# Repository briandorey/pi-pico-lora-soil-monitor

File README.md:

# Allotment LoRa Wireless Moisture Monitor

This repository contains the hardware and software files for the allotment LoRa wireless moisture monitoring system that can be found on https://www.briandorey.com/post/pi-pico-lora-remote-soil-monitor

The system consists of a sender and receiver, both using a Raspberry Pi Pico and a LoRa wireless module. The sensor reads moisuture, temperature and humitidy values from a series of sensors and sends the data wirelessly to the receiver module using the LoRa wireless protocol.

## Components
###  1. AllotmentSender
   - Hardware: Includes the design and implementation of the sender's physical components.
   - Firmware: Software running on the sender hardware to read sensor data, update an e-paper display and send the data to the home receiver via a LoRa module.

### 2. Home Receiver
   - Hardware: Details about the receiver's physical components.
   - Firmware: Software running on the receiver hardware to handle incoming LoRa data and relay it to an MQTT broker

## License

MIT License

Copyright (c) 2025 Brian Dorey

Permission is hereby granted, free of charge, to any person obtaining a copy of this software and associated documentation files (the "Software"), to deal in the Software without restriction, including without limitation the rights to use, copy, modify, merge, publish, distribute, sublicense, and/or sell copies of the Software, and to permit persons to whom the Software is furnished to do so, subject to the following conditions:

The above copyright notice and this permission notice shall be included in all copies or substantial portions of the Software.

THE SOFTWARE IS PROVIDED "AS IS", WITHOUT WARRANTY OF ANY KIND, EXPRESS OR IMPLIED, INCLUDING BUT NOT LIMITED TO THE WARRANTIES OF MERCHANTABILITY, FITNESS FOR A PARTICULAR PURPOSE AND NONINFRINGEMENT. IN NO EVENT SHALL THE AUTHORS OR COPYRIGHT HOLDERS BE LIABLE FOR ANY CLAIM, DAMAGES OR OTHER LIABILITY, WHETHER IN AN ACTION OF CONTRACT, TORT OR OTHERWISE, ARISING FROM, OUT OF OR IN CONNECTION WITH THE SOFTWARE OR THE USE OR OTHER DEALINGS IN THE SOFTWARE.

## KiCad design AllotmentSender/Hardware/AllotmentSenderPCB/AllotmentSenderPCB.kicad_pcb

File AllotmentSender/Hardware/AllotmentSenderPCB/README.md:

# Allotment Sender

This directory contains the PCB files for the sender hardware. Full details for the allotment LoRa wireless moisture monitoring system that can be found on https://www.briandorey.com/post/pi-pico-lora-remote-soil-monitor

Subdirectories

- **bom**: HTML bom showing the locations of the components on the PCB.
- **production**: Gerber files and production files needed to manufacture the board.

The PCB was designed with Kicad version 9.0.1.

## KiCad

KiCad is an open-source software suite for creating electronic circuit designs and PCB layouts. It provides tools for schematic capture, PCB layout, and 3D visualization of the design.

You can download KiCad from the official website: https://kicad.org/download/

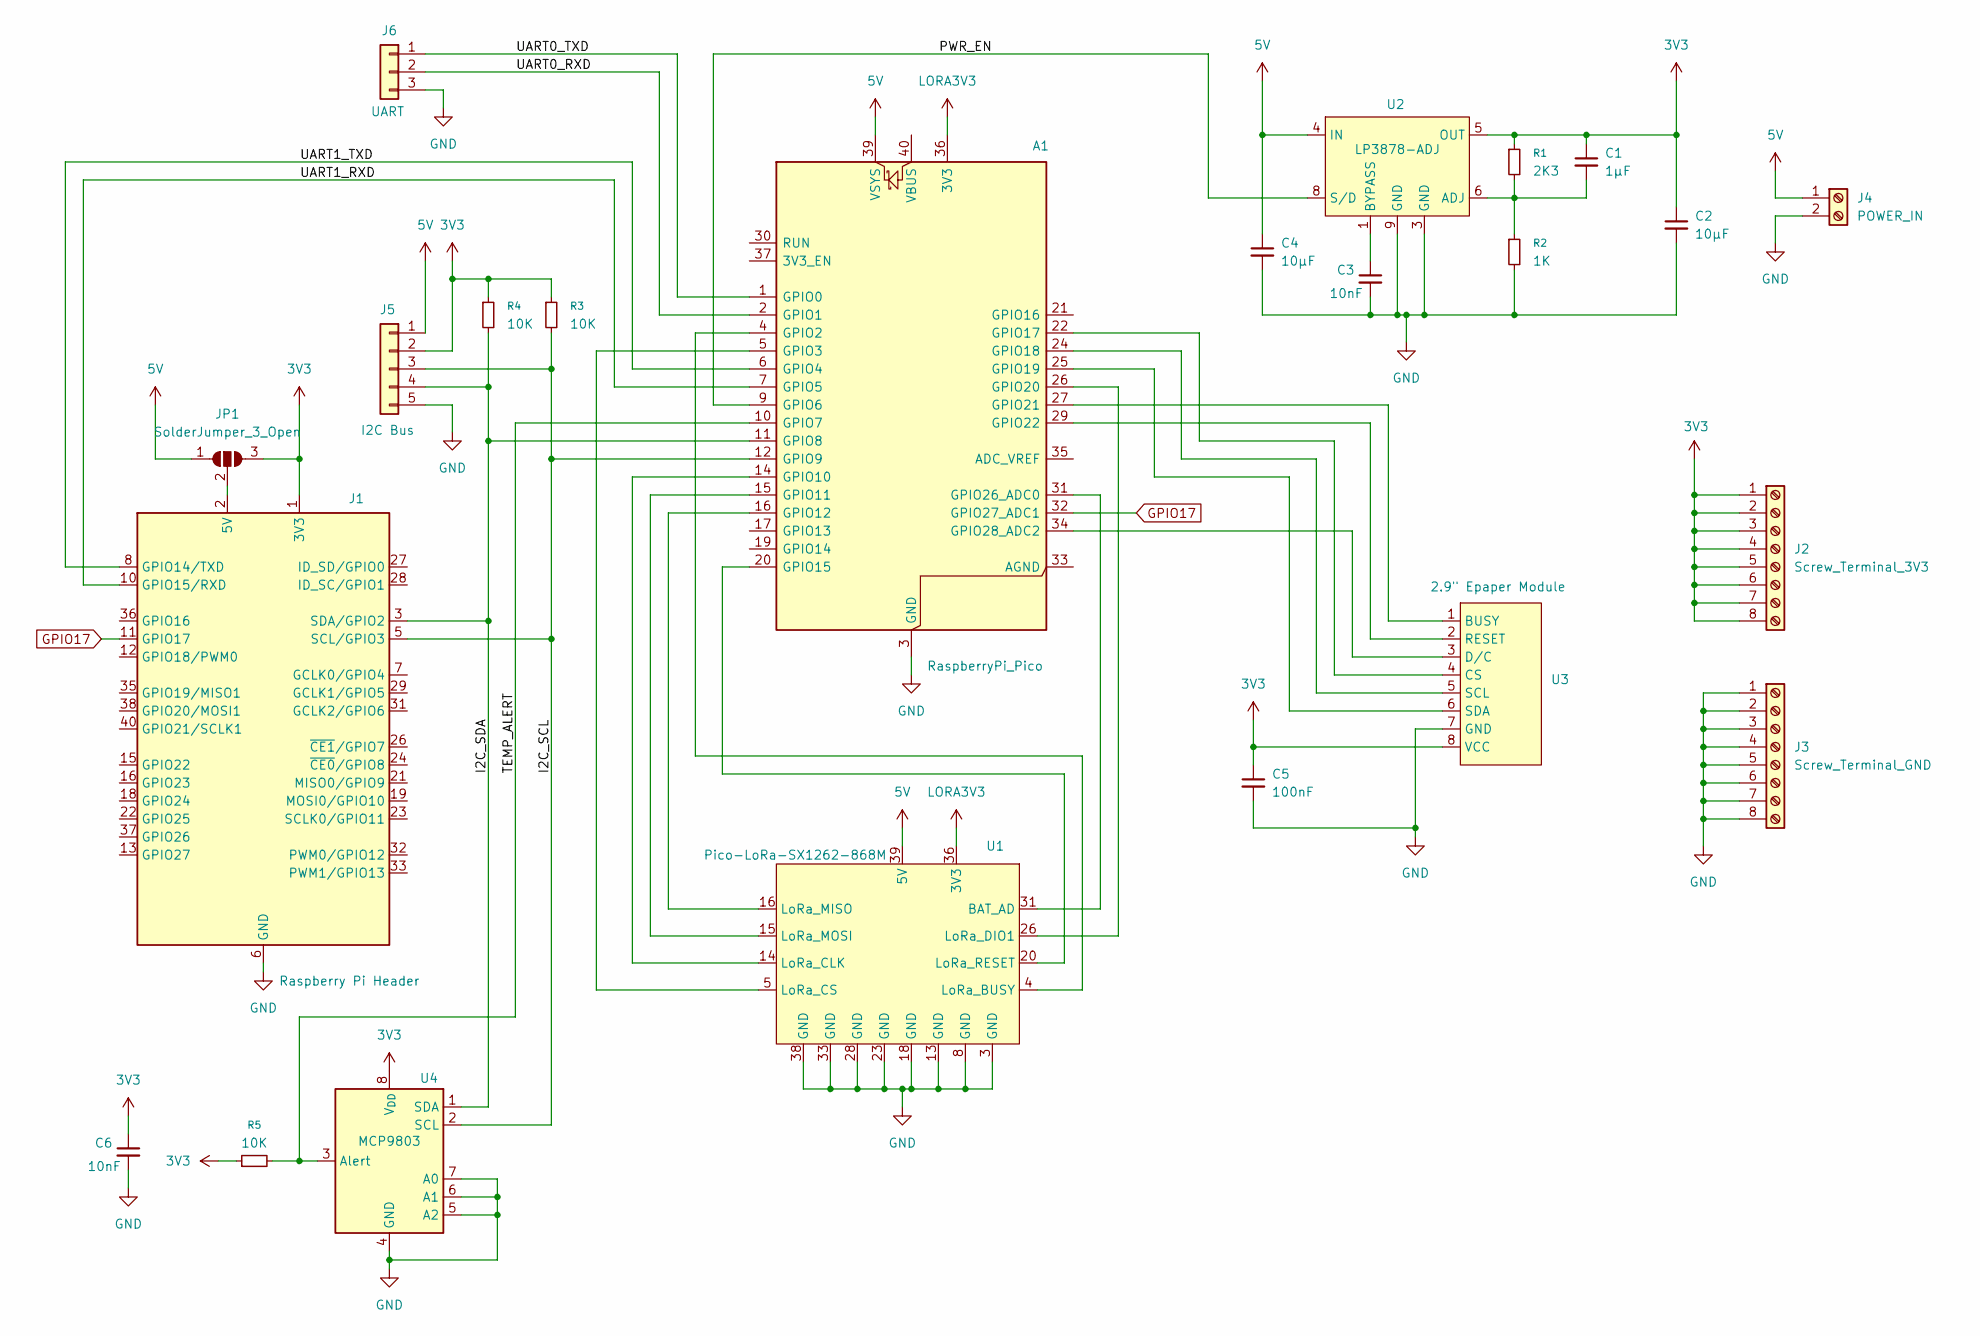
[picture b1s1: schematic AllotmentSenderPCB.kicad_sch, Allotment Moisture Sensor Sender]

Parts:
A1: RaspberryPi_Pico; RaspberryPi_Pico_Common_THT
C1: 1µF; C_0805_2012Metric
C2, C4: 10µF; C_0805_2012Metric
C3, C6: 10nF; C_0805_2012Metric
C5: 100nF; C_0805_2012Metric
J1: Raspberry Pi Header; Raspberry_Pi_Zero_Socketed_THT
J2: Screw_Terminal_3V3; PinHeader_1x08_P2.54mm_Vertical
J3: Screw_Terminal_GND; PinHeader_1x08_P2.54mm_Vertical
J4: POWER_IN; Samtec_HPM-02-01-x-S_Straight_1x02_Pitch5.08mm
J5: I2C Bus; PinHeader_1x05_P2.54mm_Vertical
J6: UART; PinHeader_1x03_P2.54mm_Vertical
JP1: SolderJumper_3_Open; PinHeader_1x03_P2.54mm_Vertical
R1: 2K3; R_0805_2012Metric
R2: 1K; R_0805_2012Metric
R3, R4, R5: 10K; R_0805_2012Metric
U1: Pico-LoRa-SX1262-868M
U2: LP3878-ADJ; SOIC-8-1EP_3.9x4.9mm_P1.27mm_EP2.41x3.81mm
U3: 2.9" Epaper Module; PinHeader_1x08_P2.54mm_Vertical
U4: MCP9803; SOIC-8_3.9x4.9mm_P1.27mm

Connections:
3V3: C1.1, C2.1, C5.1, C6.1, J1.1 (3V3), J1.17 (3V3), J2.1, J2.2, J2.3, J2.4, J2.5, J2.6, J2.7, J2.8, J5.2, JP1.3 (B), R1.1, R3.1, R4.1, R5.1, U2.5 (OUT), U3.8 (VCC), U4.8 (V_{DD})
5V: A1.39 (VSYS), C4.1, J4.1, J5.1, JP1.1 (A), U1.39 (5V), U2.4 (IN)
/I2C_SCL: A1.12 (GPIO9), J1.5 (SCL/GPIO3), J5.3, R3.2, U4.2 (SCL)
/I2C_SDA: A1.11 (GPIO8), J1.3 (SDA/GPIO2), J5.4, R4.2, U4.1 (SDA)
/PWR_EN: A1.9 (GPIO6), U2.8 (S/D)
/TEMP_ALERT: A1.10 (GPIO7), R5.2, U4.3 (Alert)
/UART0_RXD: A1.2 (GPIO1), J6.2
/UART0_TXD: A1.1 (GPIO0), J6.1
/UART1_RXD: A1.7 (GPIO5), J1.10 (GPIO15/RXD)
/UART1_TXD: A1.6 (GPIO4), J1.8 (GPIO14/TXD)
GND: A1.3 (GND), A1.8 (GND), A1.13 (GND), A1.18 (GND), A1.23 (GND), A1.28 (GND), A1.38 (GND), C2.2, C3.2, C4.2, C5.2, C6.2, J1.6 (GND), J1.9 (GND), J1.14 (GND), J1.20 (GND), J1.25 (GND), J1.30 (GND), J1.34 (GND), J1.39 (GND), J3.1, J3.2, J3.3, J3.4, J3.5, J3.6, J3.7, J3.8, J4.2, J5.5, J6.3, R2.2, U1.3 (GND), U1.8 (GND), U1.13 (GND), U1.18 (GND), U1.23 (GND), U1.28 (GND), U1.33 (GND), U1.38 (GND), U2.3 (GND), U2.9 (GND), U3.7 (GND), U4.4 (GND), U4.5 (A2), U4.6 (A1), U4.7 (A0)
GPIO17: A1.32 (GPIO27_ADC1), J1.11 (GPIO17)
LORA3V3: A1.36 (3V3), U1.36 (3V3)
unnamed: A1.4 (GPIO2), U1.4 (LoRa_BUSY)
unnamed: A1.5 (GPIO3), U1.5 (LoRa_CS)
unnamed: A1.14 (GPIO10), U1.14 (LoRa_CLK)
unnamed: A1.15 (GPIO11), U1.15 (LoRa_MOSI)
unnamed: A1.16 (GPIO12), U1.16 (LoRa_MISO)
unnamed: A1.20 (GPIO15), U1.20 (LoRa_RESET)
unnamed: A1.22 (GPIO17), U3.4 (CS)
unnamed: A1.24 (GPIO18), U3.5 (SCL)
unnamed: A1.25 (GPIO19), U3.6 (SDA)
unnamed: A1.26 (GPIO20), U1.26 (LoRa_DIO1)
unnamed: A1.27 (GPIO21), U3.1 (BUSY)
unnamed: A1.29 (GPIO22), U3.2 (RESET)
unnamed: A1.31 (GPIO26_ADC0), U1.31 (BAT_AD)
unnamed: A1.34 (GPIO28_ADC2), U3.3 (D/C)
unnamed: J1.2 (5V), J1.4 (5V), JP1.2 (C)
unnamed: C1.2, R1.2, R2.1, U2.6 (ADJ)
unnamed: C3.1, U2.1 (BYPASS)

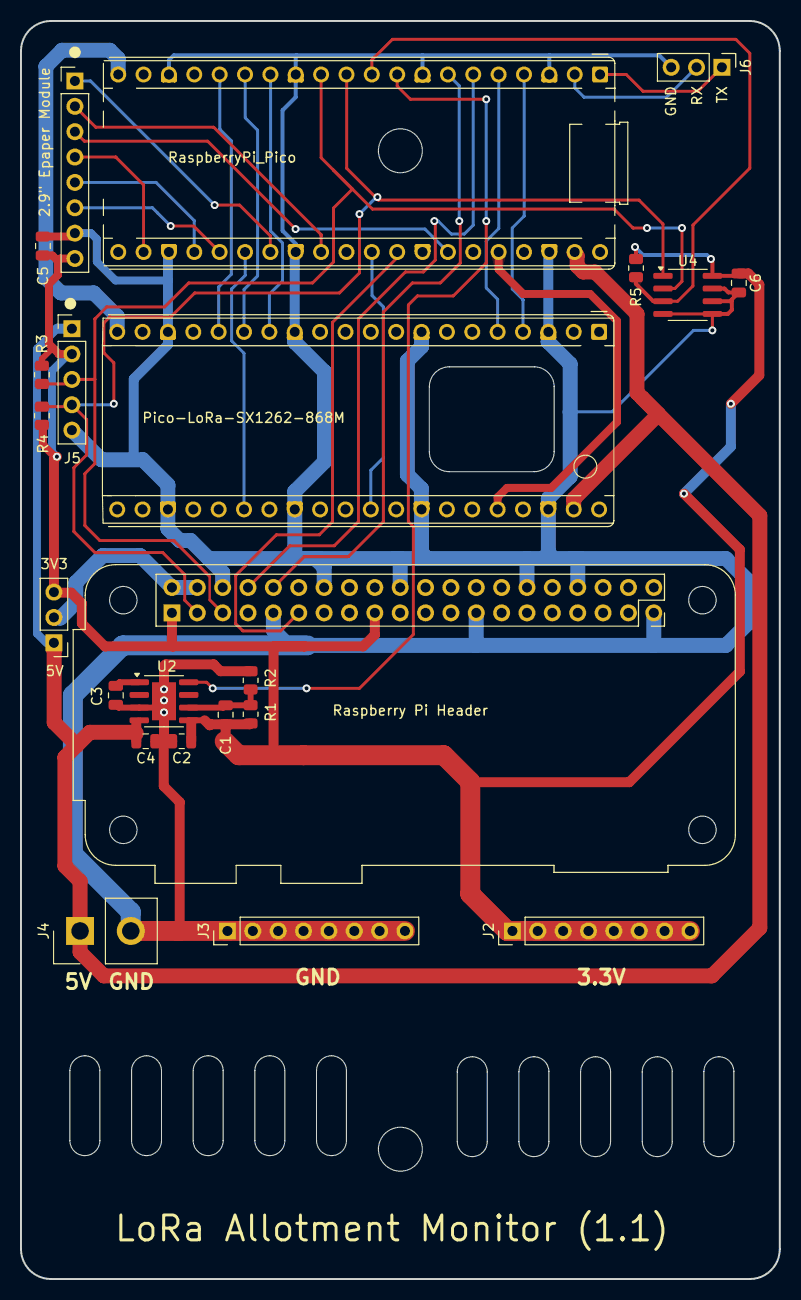
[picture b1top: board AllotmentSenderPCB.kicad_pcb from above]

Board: 2 copper layers, 76.0 x 126.0 mm, 23 parts (0 on the bottom side), 30 nets.

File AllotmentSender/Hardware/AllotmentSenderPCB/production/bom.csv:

Designator,Footprint,Quantity,Value,LCSC Part #
A1,RaspberryPi_Pico_Common_THT,1,RaspberryPi_Pico,
C1,0805,1,1µF,
"C2, C4",0805,2,10µF,
"C3, C6",0805,2,10nF,
C5,0805,1,100nF,
J1,Raspberry_Pi_Zero_Socketed_THT,1,Raspberry Pi Header,
J2,PinHeader_1x08_P2.54mm_Vertical,1,Screw_Terminal_3V3,
J3,PinHeader_1x08_P2.54mm_Vertical,1,Screw_Terminal_GND,
J4,Samtec_HPM-02-01-x-S_Straight_1x02_Pitch5.08mm,1,POWER_IN,
J5,PinHeader_1x05_P2.54mm_Vertical,1,I2C Bus,
J6,PinHeader_1x03_P2.54mm_Vertical,1,UART,
R1,0805,1,2K3,
R2,0805,1,1K,
"R3, R4, R5",0805,3,10K,
U1,Pico-LoRa-SX1262-868M,1,Pico-LoRa-SX1262-868M,
U2,SOIC-8-1EP_3.9x4.9mm_P1.27mm_EP2.41x3.81mm,1,LP3878-ADJ,
U3,PinHeader_1x08_P2.54mm_Vertical,1,"2.9"" Epaper Module",
U4,SOIC-8_3.9x4.9mm_P1.27mm,1,MCP9803,

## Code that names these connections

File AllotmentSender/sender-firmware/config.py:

# Constants
SLEEP_TIME: int = 600 # Sleep time in seconds (10 minutes)


# Reference voltages based on your calibration
V_DRY = 0.80   # Sensor voltage in dry soil (0%)
V_WET = 0.46   # Sensor voltage in wet soil (100%)
V_OPEN = 1.00  # Sensor miniumum voltage in open air
V_DISCONNECT = 0.2  # Sensor maximum voltage when disconnected
MAX_MOISTURE = 34  # Maximum calibrated moisture percentage

# Moisture Sensor Min/Max Values
MOISTURE_SENSOR_DRY = 15 # Dry moisture sensor value
MOISTURE_SENSOR_IDEAL_DRY = 20 # Ideal dry moisture sensor value
MOISTURE_SENSOR_IDEAL_WET = 35 # Ideal wet moisture sensor value
MOISTURE_SENSOR_WET = 40 # Saturated moisture sensor value

# RPI Header Pin Definitions
RPIHEADER_GPIO17 = 27 # GPIO 17 on the Raspberry Pi header - connects to GPIO27 on Raspberry Pi Pico
RPIHEADER_UART_TX = 4 # UART TX on the Raspberry Pi header - connects to GPIO4 on Raspberry Pi Pico
RPIHEADER_UART_RX = 5 # UART RX on the Raspberry Pi header - connects to GPIO5 on Raspberry Pi Pico

# E-paper Display Pin Definitions
DISPLAY_SPIBUS = 0 # SPI bus number
DISPLAY_SDA = 19 # GPIO19 on Raspberry Pi Pico
DISPLAY_SCK = 18 # GPIO18 on Raspberry Pi Pico
DISPLAY_CS = 17 # GPIO17 on Raspberry Pi Pico
DISPLAY_DC = 28 # GPIO28 on Raspberry Pi Pico
DISPLAY_RST = 22 # GPIO22 on Raspberry Pi Pico
DISPLAY_BUSY = 21 # GPIO21 on Raspberry Pi Pico

# LORA Module Pin Definitions
LORA_SPIBUS = 1 # SPI bus number
LORA_MOSI = 11 # GPIO11 on Raspberry Pi Pico
LORA_MISO = 12 # GPIO12 on Raspberry Pi Pico
LORA_CLK = 10 # GPIO10 on Raspberry Pi Pico
LORA_CS = 3 # GPIO3 on Raspberry Pi Pico
LORA_RST = 15 # GPIO15 on Raspberry Pi Pico
LORA_GPIO = 2 # GPIO2 on Raspberry Pi Pico 
LORA_IRQ = 20 # GPIO20 on Raspberry Pi Pico

# I2C Bus Pin Definitions
# The I2C bus is used for communication with the AHT20 and MCP9803 sensors.
I2C_BUS = 0 # I2C bus number
I2C_SDA = 8 # GPIO8 on Raspberry Pi Pico
I2C_SCL = 9 # GPIO9 on Raspberry Pi Pico
I2C_FREQ = 100000 # I2C frequency

# LoRa Configuration Constants
# These constants are used to configure the LoRa module and should be set according to your requirements.
LORA_FREQUENCY=868 # Frequency in MHz
LORA_BANDWIDTH=500.0 # Bandwidth in kHz
LORA_SPREADINGFACTOR=12 # Spreading factor (7-12)
LORA_CODINGRATE=8 # Coding rate (5-8)
LORA_SYNCWORD=0x18 # Sync word for private networks
LORA_POWER=-9 # Transmit power in dBm
LORA_MAX_POWER=22 # Maximum transmit power in dBm
LORA_CURRENTLIMIT=60.0 # Current limit in mA
LORA_PREAMBLELENGTH=8 # Preamble length in symbols

# Define minimum acceptable SNR for communication
# The SNR (Signal-to-Noise Ratio) is a measure of signal quality.
# The LoRa power output will be increased until the SNR is above this threshold.
# This value should be adjusted based on your specific requirements
# and the environment in which the LoRa module operates.
# A higher value means a stronger signal is required for successful communication.
MIN_SNR = -20

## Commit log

2025-05-17 Upload Files
